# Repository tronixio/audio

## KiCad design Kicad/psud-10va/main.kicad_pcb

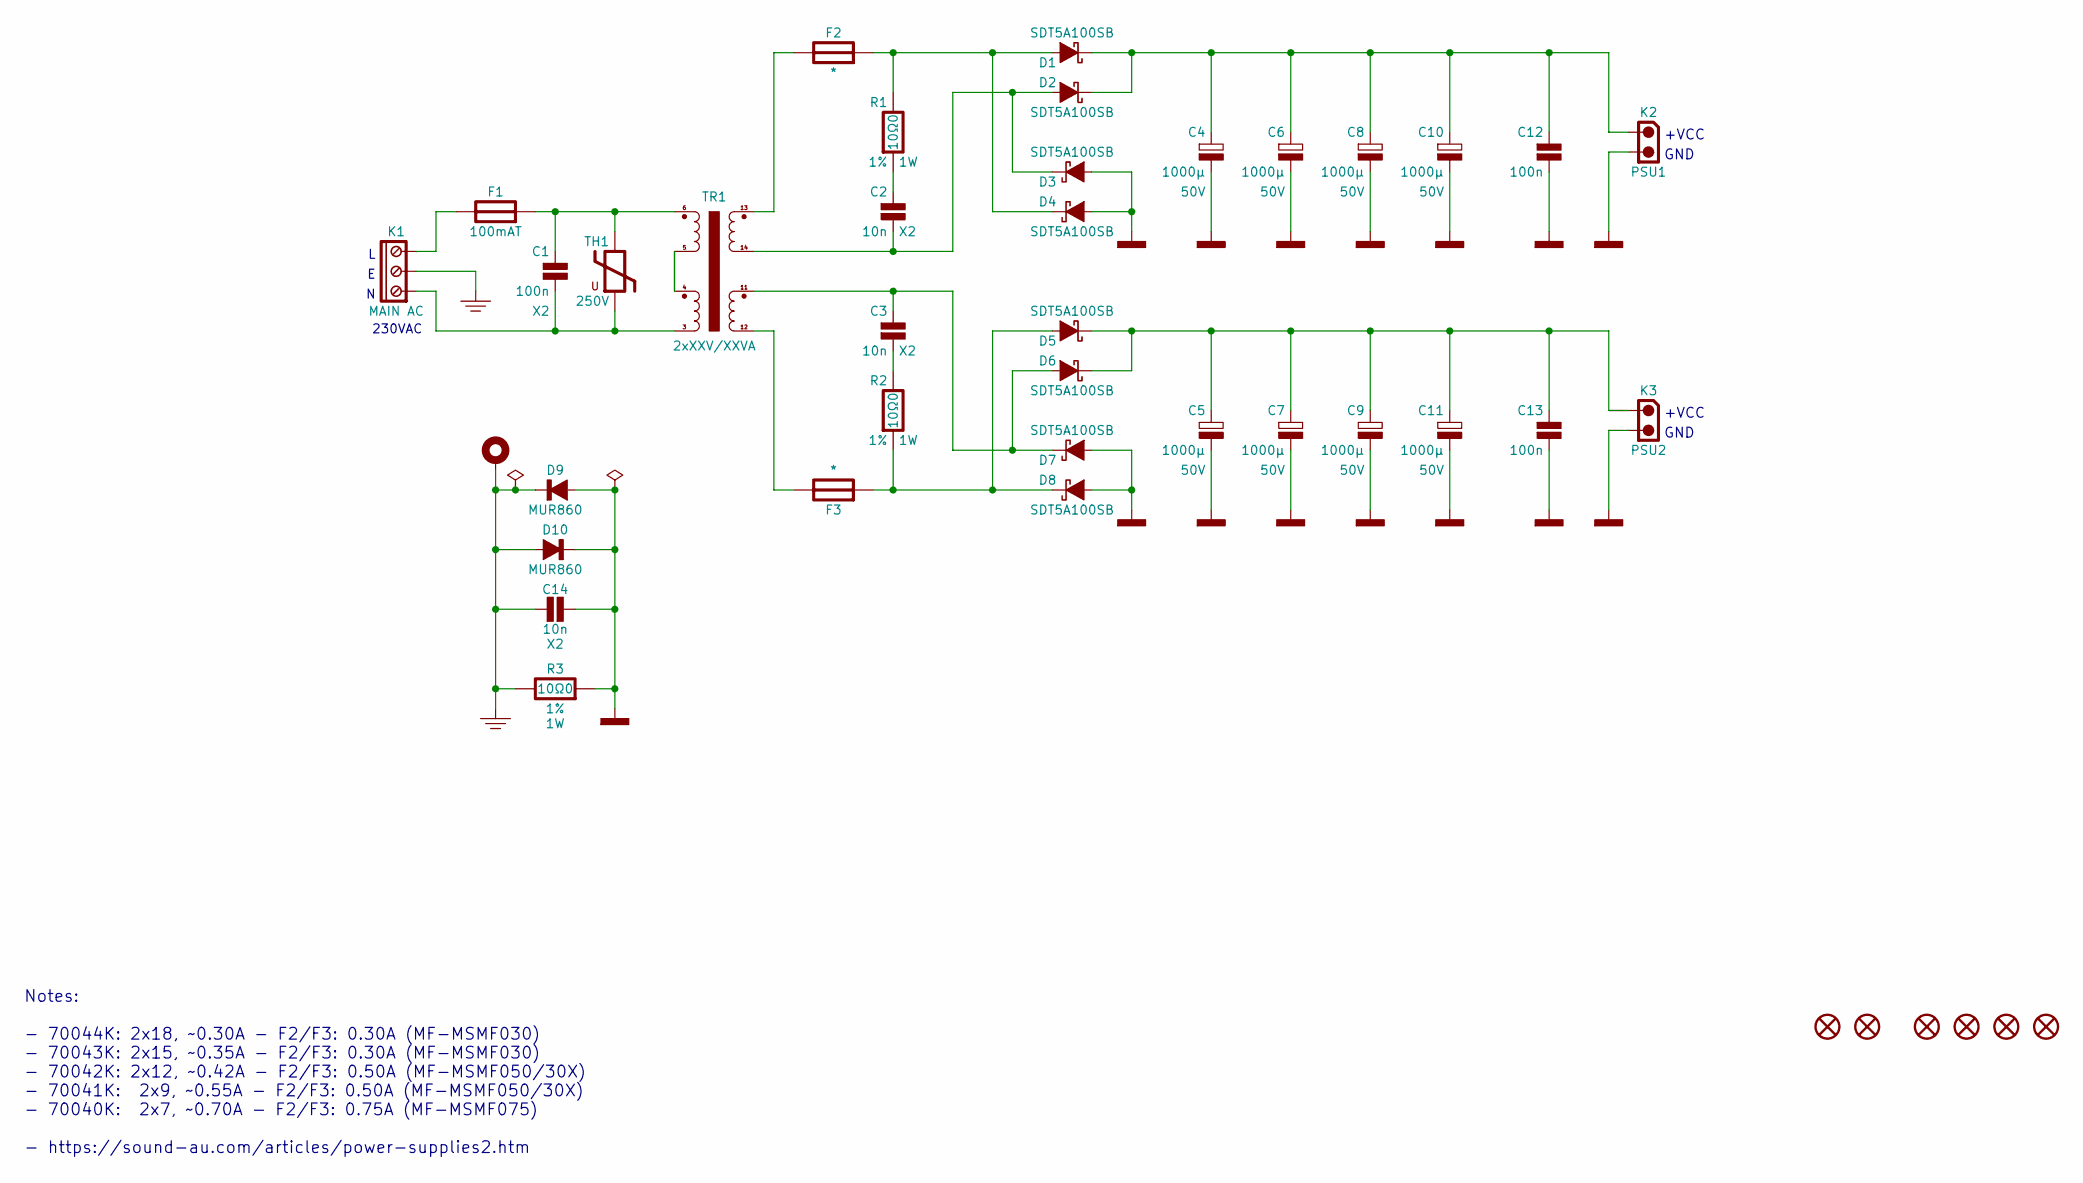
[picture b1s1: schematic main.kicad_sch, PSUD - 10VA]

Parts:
C1: 100n; WURTH-890324025017; Tolerance 10%; Voltage 275VAC; Mouser 710-890324025017
C2, C3, C14: 10n; CAPACITOR-SMD-2220; Tolerance 10%; Voltage 250VAC; Mouser 77-VJ2220Y103KXUSTX2
C4, C5, C6, C7, C8, C9, C10, C11: 1000µ; CAPACITOR-ELECTROLYTIC-RADIAL-130-250-050-WURTH; Tolerance 20%; Voltage 50V; Mouser 710-860010678024
C12, C13: 100n; CAPACITOR-SMD-1206; Tolerance 5%; Voltage 50V; Mouser 80-C1206C104J5R
D1, D2, D3, D4, D5, D6, D7, D8: SDT5A100SB; DIODE-SMB; Part Marking DXA; Mouser 621-SDT5A100SB-13
D9, D10: MUR860; DIODE-SMC; Part Marking 860JS; Mouser 771-MUR860J
F1: 100mAT; KEYSTONE-4628; Mouser 534-4628
F2, F3: *; FUSE-SMD-1812; Part Marking 75xx; Mouser 652-MF-MSMF075/24-2
F4: 100mA/SB; FUSE-CARTRIDGE-5X20; Mouser 576-0239.100MXP
F5: KEYSTONE-4628C; Mouser 534-4628C
H1: MOUNTING-HOLE-3MM-PAD-VIA
H2, H3, H4, H5: MOUNTING-HOLE-3MM-MASK
K1: MAIN AC; SAMESKY-TB005-762-03BE; Mouser 490-TB005-762-03BE
K2: PSU1; MOLEX-559320230; Mouser 538-55932-0230
K3: PSU2; MOLEX-559320230; Mouser 538-55932-0230
R1, R2, R3: 10Ω0; RESISTOR-SMD-2512; Tolerance 1%; Mouser 603-RC2512FK-0710RL
TH1: 250V; BOURNS-VARISTOR-ISOM3; Mouser 652-ISOM3-250-B-L2
TR1: 2xXXV/XXVA; TALEMA-TRANSFORMER-10VA

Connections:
EARTH: C14.1, D9.1 (C), D10.2 (A), H1.1, K1.2, R3.1
GND: C4.2, C5.2, C6.2, C7.2, C8.2, C9.2, C10.2, C11.2, C12.2, C13.2, C14.2, D3.2 (A), D4.2 (A), D7.2 (A), D8.2 (A), D9.2 (A), D10.1 (C), K2.2, K3.2, R3.2
unnamed: C1.1, F1.2, TH1.1, TR1.6
unnamed: C1.2, K1.1, TH1.2, TR1.3
unnamed: C2.1, R1.2
unnamed: C3.2, R2.1
unnamed: D1.2 (A), D4.1 (C), F2.2, R1.1
unnamed: C4.1, C6.1, C8.1, C10.1, C12.1, D1.1 (C), D2.1 (C), K2.1
unnamed: C2.2, D2.2 (A), D3.1 (C), TR1.14
unnamed: D5.2 (A), D8.1 (C), F3.2, R2.2
unnamed: C5.1, C7.1, C9.1, C11.1, C13.1, D5.1 (C), D6.1 (C), K3.1
unnamed: C3.1, D6.2 (A), D7.1 (C), TR1.11
unnamed: F1.1, K1.3
unnamed: F2.1, TR1.13
unnamed: F3.1, TR1.12
unnamed: TR1.4, TR1.5

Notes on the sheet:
+VCC
230VAC
GND
Notes: - 70044K: 2x18, ~0.30A - F2/F3: 0.30A (MF-MSMF030) - 70043K: 2x15, ~0.35A - F2/F3: 0.30A (MF-MSMF030) - 70042K: 2x12, ~0.42A - F2/F3: 0.50A (MF-MSMF050/30X) - 70041K: 2x9, ~0.55A - F2/F3: 0.50A (MF-MSMF050/30X) - 70040K: 2x7, ~0.70A - F2/F3: 0.75A (MF-MSMF075) - https://sound-au.com/articles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

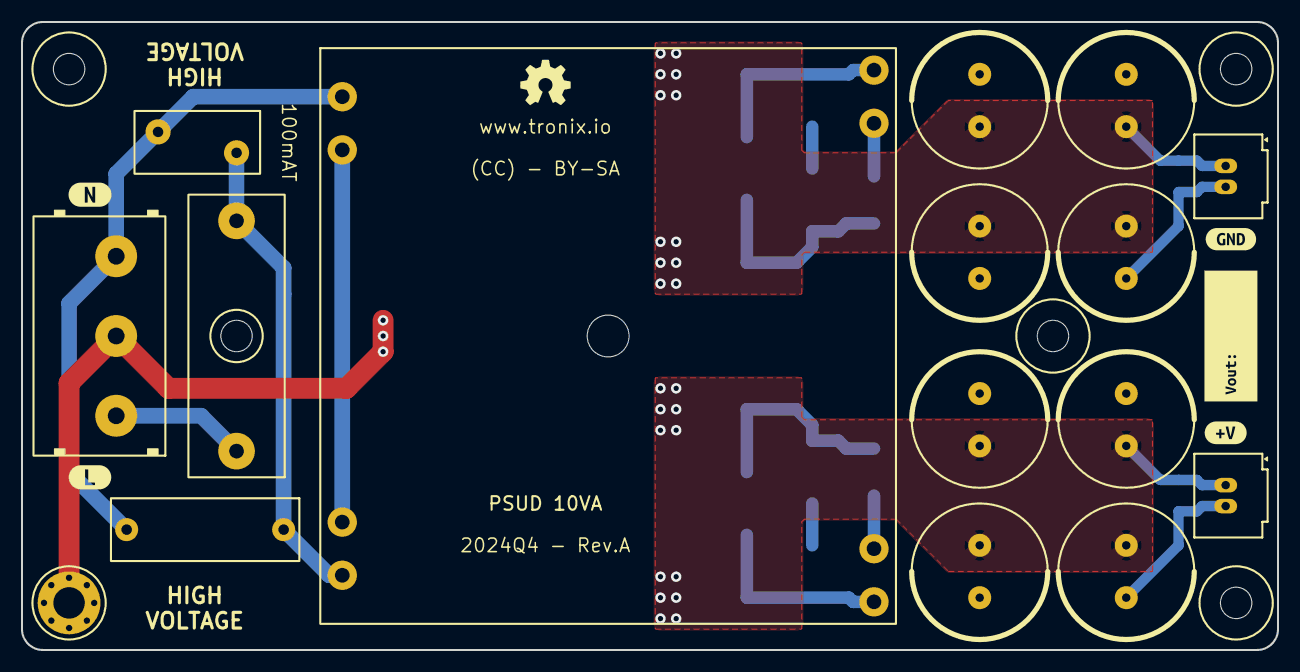
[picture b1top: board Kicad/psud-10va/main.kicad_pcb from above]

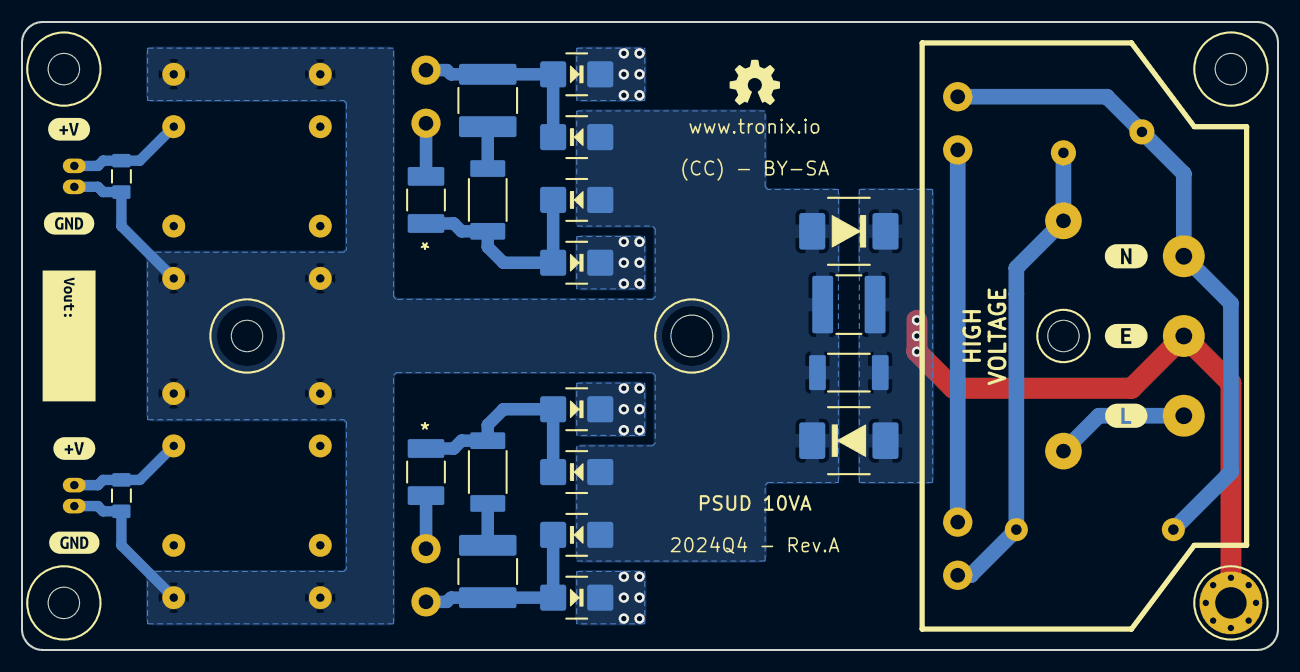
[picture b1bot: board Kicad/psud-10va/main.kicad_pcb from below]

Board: 2 copper layers, 120.0 x 60.0 mm, 57 parts (29 on the bottom side), 16 nets.

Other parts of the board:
X101, X101#2: LOGO; OSHW-5MM
kibuzzard-65E1EBC7, kibuzzard-65E1EBC7#2: G***; kibuzzard-65E1EBC7
kibuzzard-65E1EBD0, kibuzzard-65E1EBD0#2: G***; kibuzzard-65E1EBD0
kibuzzard-67C2FE8F: G***; kibuzzard-67C2FE8F
kibuzzard-67C315A4: G***; kibuzzard-67C315A4
kibuzzard-67C31590: G***; kibuzzard-67C31590
kibuzzard-67C31596: G***; kibuzzard-67C31596
kibuzzard-6735E4BF: G***; kibuzzard-6735E4BF
kibuzzard-6735E49C: G***; kibuzzard-6735E49C
kibuzzard-66229E9D, kibuzzard-66229E9D#2, kibuzzard-66229E9D#3: G***; kibuzzard-66229E9D

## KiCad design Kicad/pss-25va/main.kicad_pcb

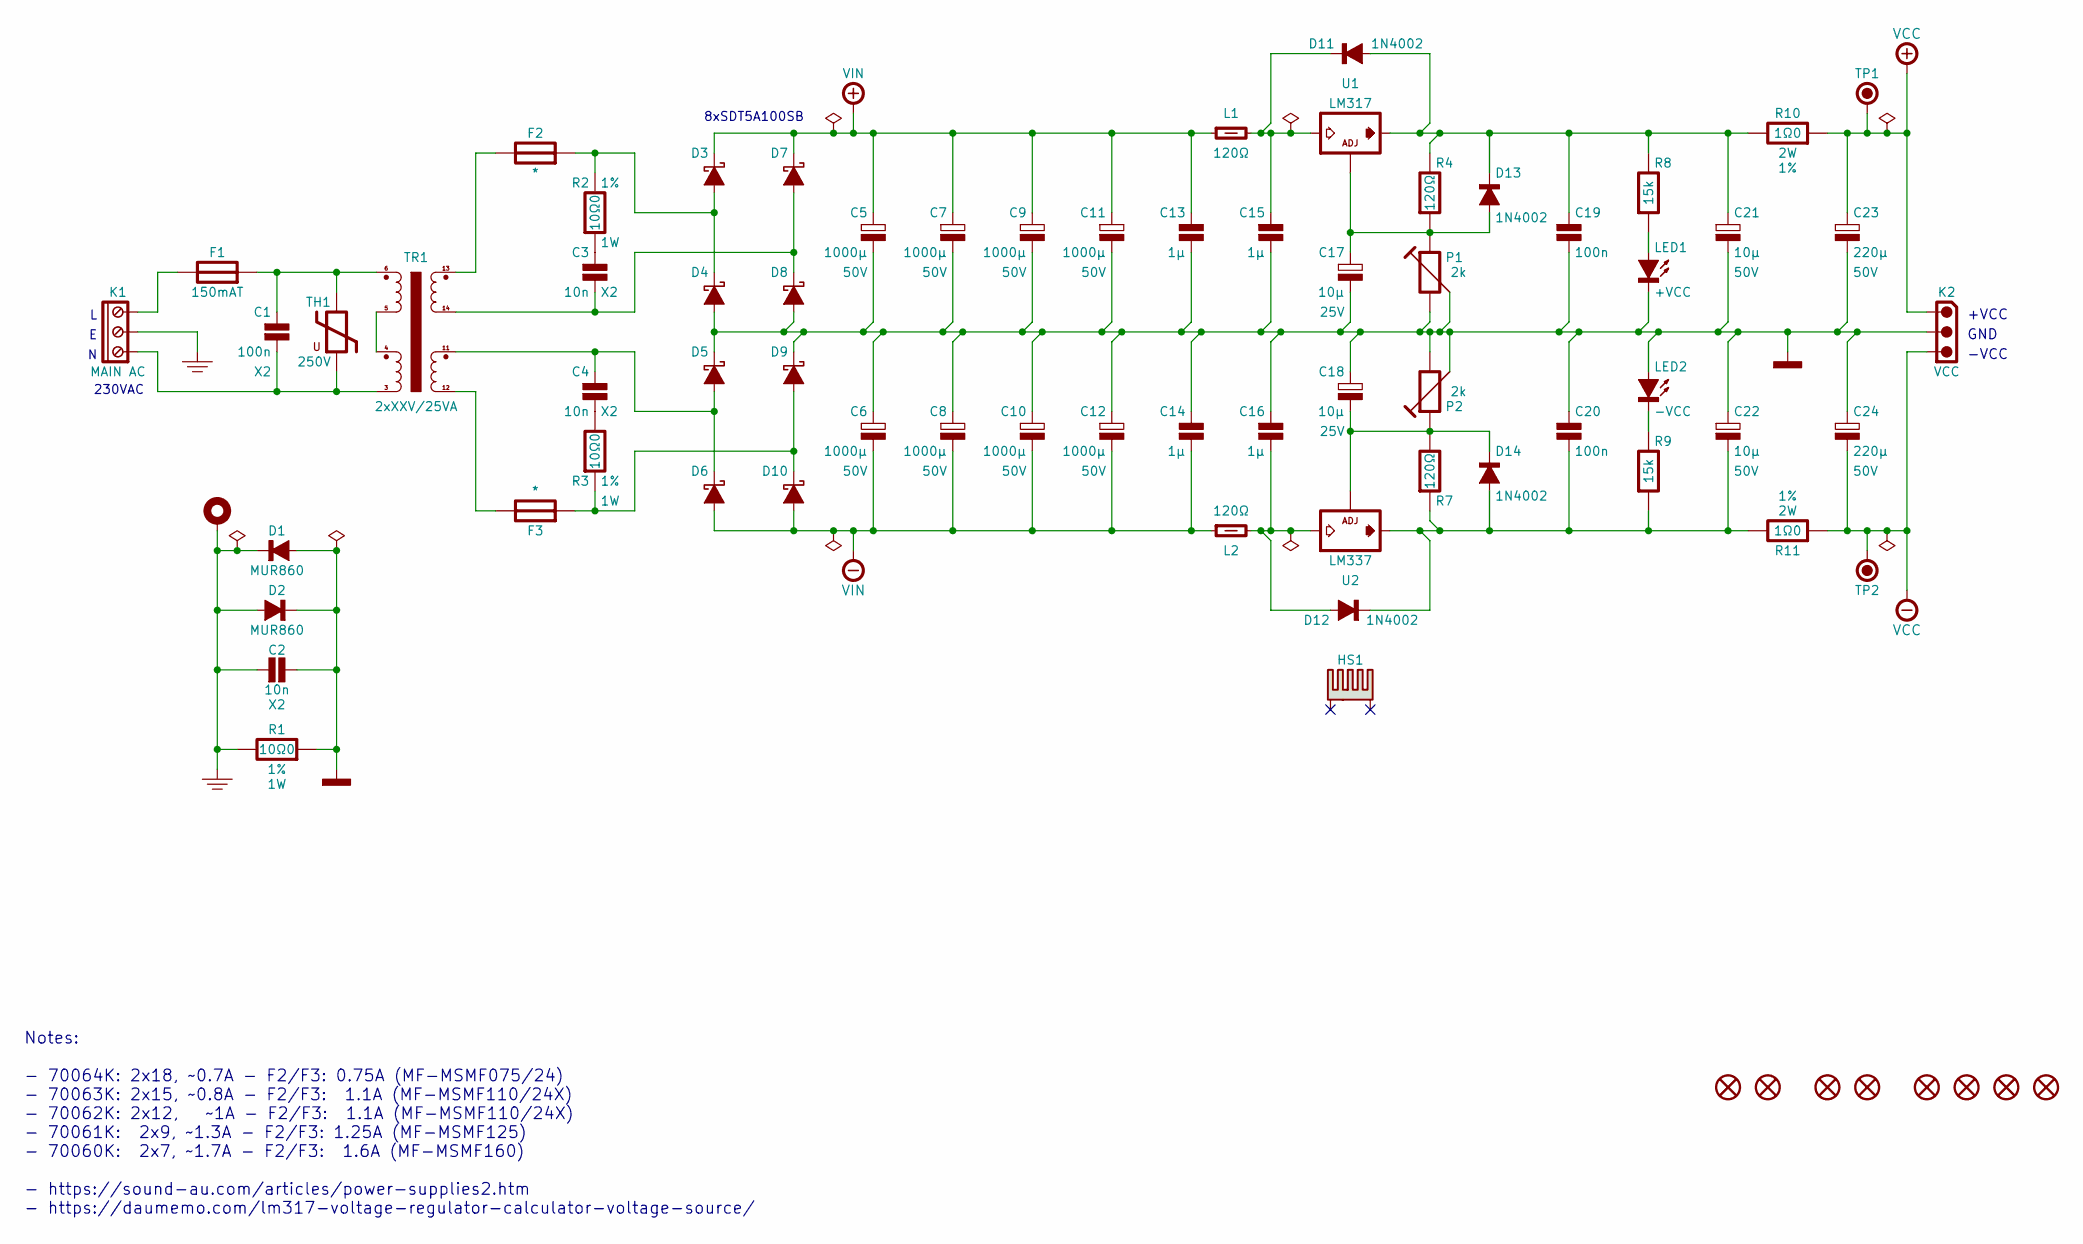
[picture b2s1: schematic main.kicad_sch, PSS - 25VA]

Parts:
C1: 100n; WURTH-890324025017; Tolerance 10%; Voltage 275VAC; Mouser 710-890324025017
C2, C3, C4: 10n; CAPACITOR-SMD-2220; Tolerance 10%; Voltage 250VAC; Mouser 77-VJ2220Y103KXUSTX2
C5, C6, C7, C8, C9, C10, C11, C12: 1000µ; CAPACITOR-ELECTROLYTIC-RADIAL-130-250-050-WURTH; Tolerance 20%; Voltage 50V; Mouser 710-860010678024
C13, C14, C15, C16: 1µ; CAPACITOR-SMD-1206; Tolerance 5%; Voltage 50V; Mouser 80-C1206C105J5
C17, C18: 10µ; CAPACITOR-SMD-CASE-B; Voltage 25V; Tolerance 10%; Mouser 74-293D106X9025B2TE3
C19, C20: 100n; CAPACITOR-SMD-1206; Tolerance 5%; Voltage 50V; Mouser 80-C1206C104J5R
C21, C22: 10µ; CAPACITOR-ELECTROLYTIC-RADIAL-050-110-020-WURTH; Tolerance 20%; Voltage 50V; Mouser 710-860240672002
C23, C24: 220µ; CAPACITOR-ELECTROLYTIC-RADIAL-100-125-050-WURTH; Tolerance 20%; Voltage 50V; Mouser 710-860010675018
D1, D2: MUR860; DIODE-SMC; Part Marking 860JS; Mouser 771-MUR860J
D3, D4, D5, D6, D7, D8, D9, D10: SDT5A100SB; DIODE-SMB; Part Marking DXA; Mouser 621-SDT5A100SB-13
D11, D12, D13, D14: 1N4002; DIODE-SMA; Part Marking A2; Mouser 583-FM4002
F1: 150mAT; KEYSTONE-4628; Mouser 534-4628
F2, F3: *; FUSE-SMD-1812; Part Marking 75xx; Mouser 652-MF-MSMF075/24-2
F4: 150mA/SB; FUSE-CARTRIDGE-5X20; Mouser 576-0239.150MXP
F5: KEYSTONE-4628C; Mouser 534-4628C
H1: MOUNTING-HOLE-3MM-PAD-VIA
H2, H3, H4, H5: MOUNTING-HOLE-3MM-MASK
HS1: OHMITE-C220-050; Mouser 588-C220-050-2AE
K1: MAIN AC; SAMESKY-TB005-762-03BE; Mouser 490-TB005-762-03BE
K2: VCC; MOLEX-559320330; Mouser 538-55932-0330
L1, L2: 120Ω; INDUCTOR-SMD-1206; Mouser 81-BLM31PG121SN1L
LED1: +VCC; LED-SMD-1206; Mouser 604-APT3216LVBCD
LED2: -VCC; LED-SMD-1206; Mouser 604-APT3216LVBCD
P1, P2: 2k; BOURNS-3314J1; Tolerance 20%; Mouser 652-3314J-1-202E
R1, R2, R3: 10Ω0; RESISTOR-SMD-2512; Tolerance 1%; Mouser 603-RC2512FK-0710RL
R4, R7: 120Ω; RESISTOR-SMD-1206; Tolerance 5%; Mouser 603-RT1206FRE07120RL
R8, R9: 15k; RESISTOR-SMD-1206; Tolerance 5%; Mouser 660-RK73B2BTTDD153J
R10, R11: 1Ω0; RESISTOR-SMD-2512; Tolerance 1%; Mouser 652-CRS2512FW1R00ELF
TH1: 250V; BOURNS-VARISTOR-ISOM3; Mouser 652-ISOM3-250-B-L2
TH2, TH3: SP400-TO200; Mouser 951-SP400-009-00-54
TP1: +VCC; TRONIXIO-TP
TP2: -VCC; TRONIXIO-TP
TR1: 2xXXV/25VA; TALEMA-TRANSFORMER-25VA
U1: LM317; TO-220-3-VERTICAL; Mouser 863-LM317TG
U2: LM337; TO-220-3-VERTICAL; Mouser 863-LM337BTG

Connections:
+VCC: C23.1, K2.1, R10.2, TP1.1
+VIN: C5.1, C7.1, C9.1, C11.1, C13.1, D3.1 (C), D7.1 (C), L1.1
-VCC: C24.2, K2.3, R11.2, TP2.1
-VIN: C6.2, C8.2, C10.2, C12.2, C14.2, D6.2 (A), D10.2 (A), L2.1
EARTH: C2.1, D1.1 (C), D2.2 (A), H1.1, K1.2, R1.1
GND: C2.2, C5.2, C6.1, C7.2, C8.1, C9.2, C10.1, C11.2, C12.1, C13.2, C14.1, C15.2, C16.1, C17.2, C18.1, C19.2, C20.1, C21.2, C22.1, C23.2, C24.1, D1.2 (A), D2.1 (C), D4.2 (A), D5.1 (C), D8.2 (A), D9.1 (C), K2.2, LED1.1 (C), LED2.2 (A), P1.1, P1.2, P2.1, P2.2, R1.2
unnamed: C1.1, F1.2, TH1.1, TR1.6
unnamed: C1.2, K1.1, TH1.2, TR1.3
unnamed: C3.1, R2.2
unnamed: C4.2, R3.1
unnamed: D3.2 (A), D4.1 (C), F2.2, R2.1
unnamed: C4.1, D5.2 (A), D6.1 (C), TR1.11
unnamed: C3.2, D7.2 (A), D8.1 (C), TR1.14
unnamed: D9.2 (A), D10.1 (C), F3.2, R3.2
unnamed: C19.1, C21.1, D11.2 (A), D13.1 (C), R4.1, R8.1, R10.1, U1.2 (VOUT)
unnamed: C15.1, D11.1 (C), L1.2, U1.3 (VIN)
unnamed: C16.2, D12.2 (A), L2.2, U2.2 (VIN)
unnamed: C20.2, C22.2, D12.1 (C), D14.2 (A), R7.2, R9.2, R11.1, U2.3 (VOUT)
unnamed: C17.1, D13.2 (A), P1.3, R4.2, U1.1 (ADJ)
unnamed: C18.2, D14.1 (C), P2.3, R7.1, U2.1 (ADJ)
unnamed: F1.1, K1.3
unnamed: F2.1, TR1.13
unnamed: F3.1, TR1.12
unnamed: LED1.2 (A), R8.2
unnamed: LED2.1 (C), R9.1
unnamed: TR1.4, TR1.5

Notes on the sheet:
8xSDT5A100SB
230VAC
GND
-VCC
+VCC
Notes: - 70064K: 2x18, ~0.7A - F2/F3: 0.75A (MF-MSMF075/24) - 70063K: 2x15, ~0.8A - F2/F3: 1.1A (MF-MSMF110/24X) - 70062K: 2x12, ~1A - F2/F3: 1.1A (MF-MSMF110/24X) - 70061K: 2x9, ~1.3A - F2/F3: 1.25A (MF-MSMF125) - 70060K: 2x7, ~1.7A - F2/F3: 1.6A (MF-MSMF160) - https://sound-au.com/articles/power-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

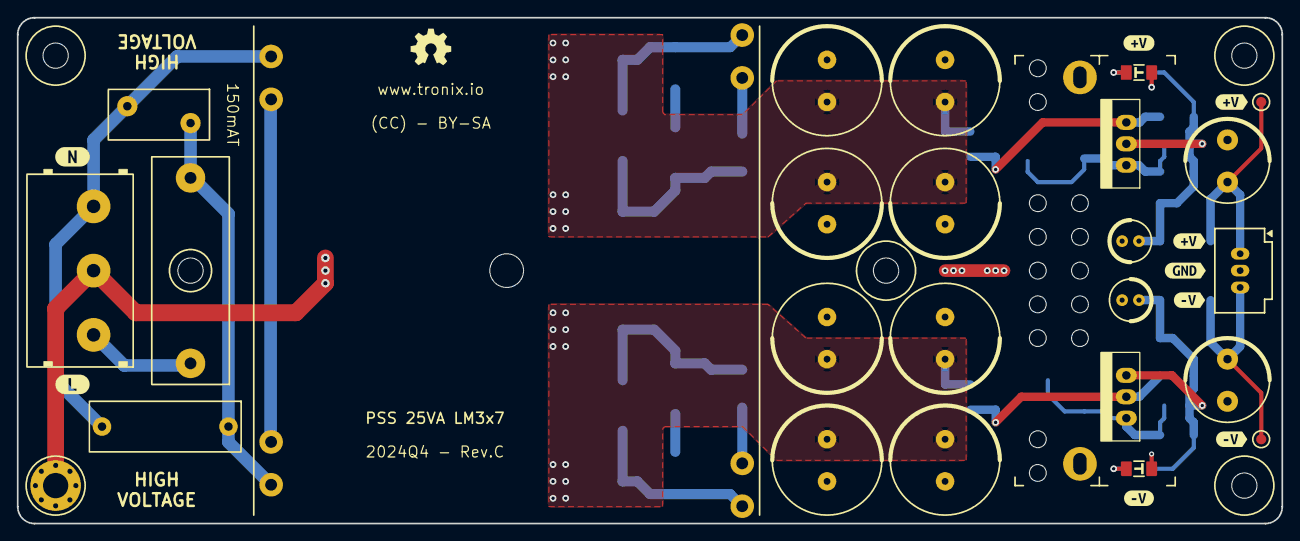
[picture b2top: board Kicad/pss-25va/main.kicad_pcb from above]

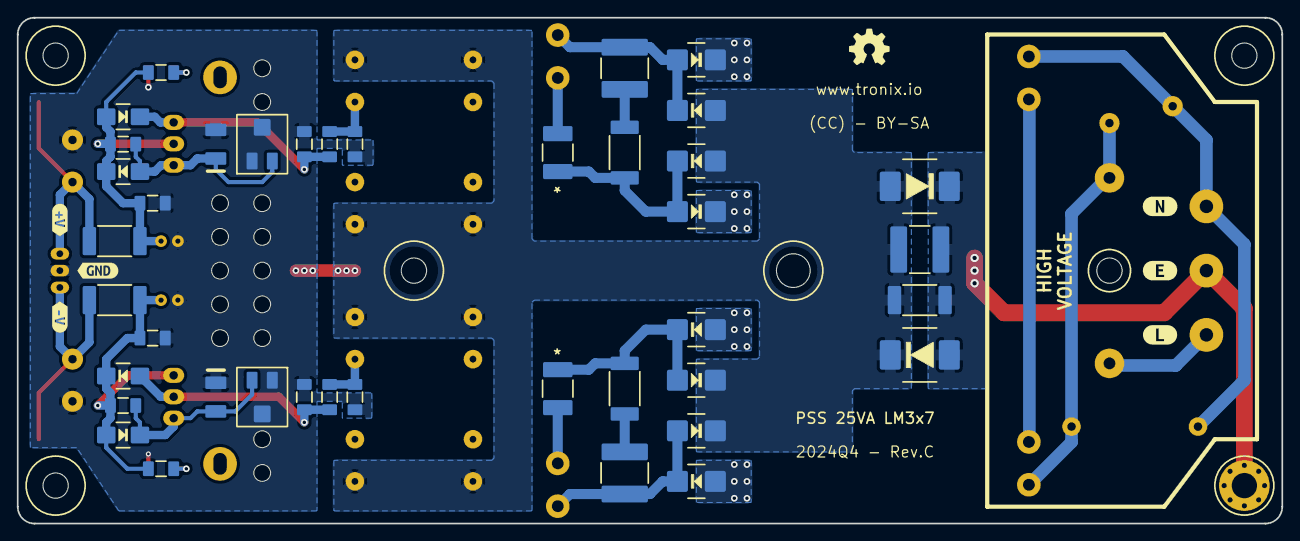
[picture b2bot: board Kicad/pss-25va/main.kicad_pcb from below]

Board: 2 copper layers, 150.0 x 60.0 mm, 89 parts (47 on the bottom side), 26 nets.

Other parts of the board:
X101, X101#2: LOGO; OSHW-5MM
kibuzzard-65E1EBC7, kibuzzard-65E1EBC7#2: G***; kibuzzard-65E1EBC7
kibuzzard-65E1EBD0, kibuzzard-65E1EBD0#2: G***; kibuzzard-65E1EBD0
kibuzzard-67C370B6: G***; kibuzzard-67C370B6
kibuzzard-67C370BE: G***; kibuzzard-67C370BE
kibuzzard-67C370C7: G***; kibuzzard-67C370C7
kibuzzard-67C370CF: G***; kibuzzard-67C370CF
kibuzzard-67C370D9: G***; kibuzzard-67C370D9
kibuzzard-67C370DF: G***; kibuzzard-67C370DF
kibuzzard-67C3709C: G***; kibuzzard-67C3709C
kibuzzard-67C36920: G***; kibuzzard-67C36920
kibuzzard-67C37093: G***; kibuzzard-67C37093
kibuzzard-6649FA9C: G***; kibuzzard-6649FA9C
kibuzzard-6649FAAE: G***; kibuzzard-6649FAAE

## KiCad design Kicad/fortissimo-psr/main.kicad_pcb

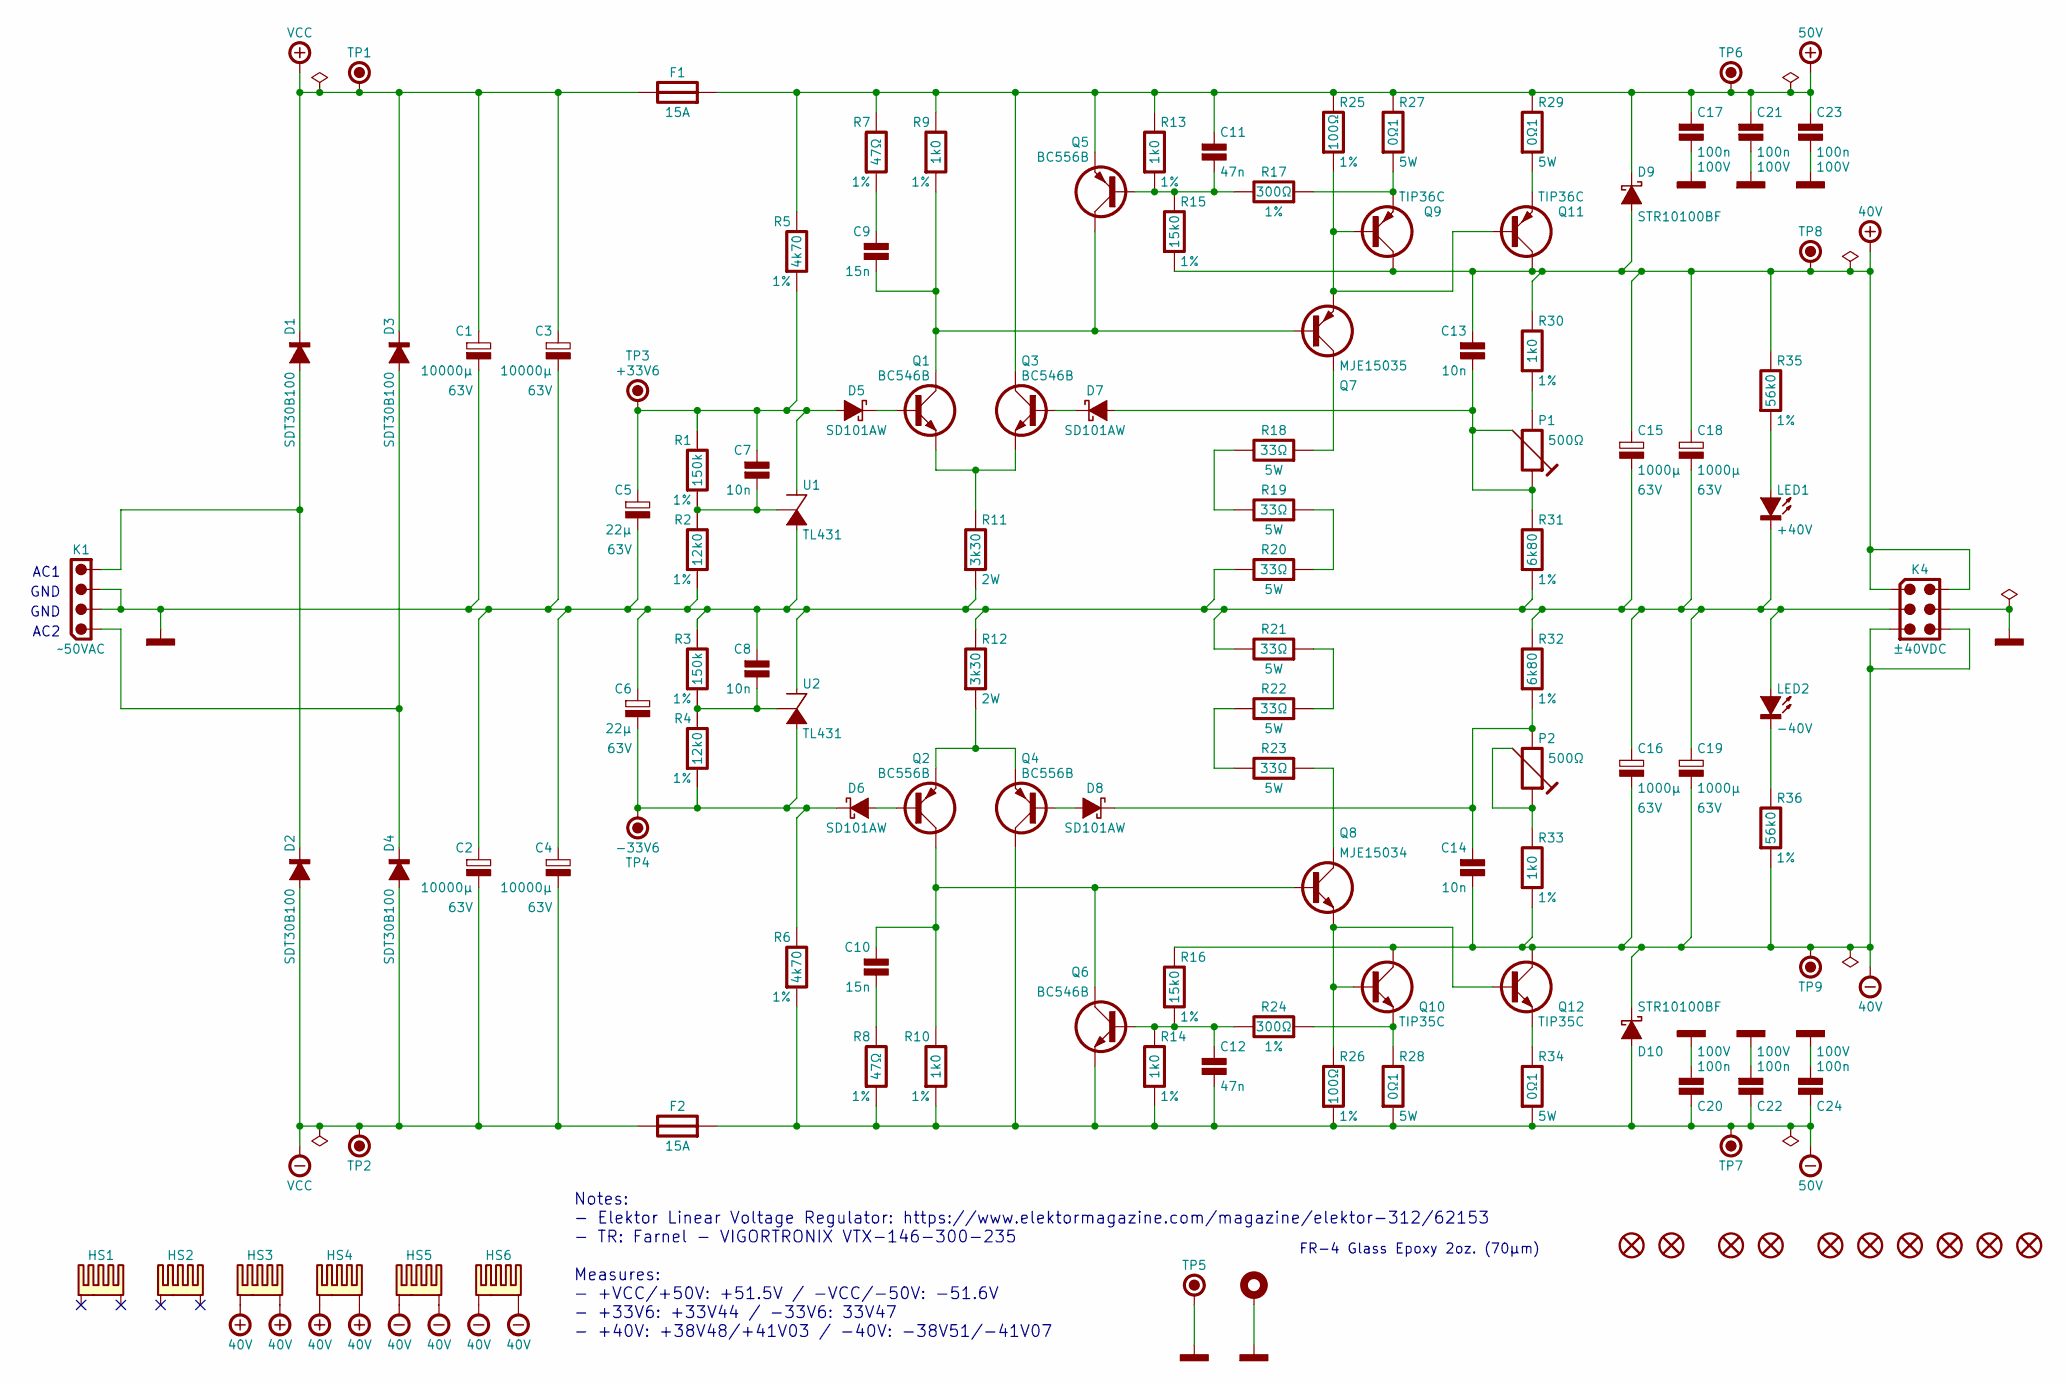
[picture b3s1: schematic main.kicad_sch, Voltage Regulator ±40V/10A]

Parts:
C1, C2, C3, C4: 10000µ; CAPACITOR-ELECTROLYTIC-RADIAL-350-520-010-WURTH; Tolerance 20%; Voltage 63V; Mouser 710-861140786024
C5, C6: 22µ; CAPACITOR-ELECTROLYTIC-RADIAL-063-110-025-WURTH; Voltage 63V; Tolerance 20%; Mouser 710-860080773004
C7, C8, C13, C14: 10n; CAPACITOR-SMD-1206; Voltage 100V; Tolerance 5%; Mouser 80-C1206C103J1R
C9, C10: 15n; CAPACITOR-SMD-1206; Voltage 100V; Tolerance 5%; Mouser 81-GRM3195C2A153JA1D
C11, C12: 47n; CAPACITOR-SMD-1206; Tolerance 5%; Voltage 100V; Mouser 603-CC126JRX7R0BB473
C15, C16, C18, C19: 1000µ; CAPACITOR-ELECTROLYTIC-RADIAL-160-250-075-WURTH; Tolerance 20%; Voltage 63V; Mouser 661-EKYB630E102ML25S
C17, C20, C21, C22, C23, C24: 100n; CAPACITOR-SMD-1206; Tolerance 5%; Voltage 100V; Mouser 80-C1206C104J1R7210
D1, D2, D3, D4: SDT30B100; TO-252-2; Mouser 621-SDT30B100D1-13
D5, D6, D7, D8: SD101AW; SOD-123; Part Marking S1/SK; Mouser 621-SD101AW-F
D9, D10: STR10100BF; DIODE-SMBF; Mouser 241-STR10100BFR10701
F1, F2: 15A; SCHURTER-OGN-3132874; Mouser 693-3-132-874
F3, F4: 15A; FUSE-CARTRIDGE-5X20; Mouser 576-0215015.MXP
H1: GND; MOUNTING-HOLE-3MM-PAD-VIA
HS1, HS2: HSE19-361616P; SAMESKY-HSE19-361616P; Mouser 179-HSE19-361616P
HS3, HS4, HS5, HS6: WAKEFIELD-657-25ABEP; Mouser 567-657-25ABEP
K1: ~50VAC; MOLEX-532580429; Mouser 538-53258-0429
K2: MIGHTY-SPOX; MOLEX-510670400; Mouser 538-51067-0400 / 538-50217-8000-CT / 53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
K3: MINI-FIT; MOLEX-39012060; Mouser 538-39-01-2060 / 538-39-00-0039 / 538-3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
K4: ±40VDC; MOLEX-39288060; Mouser 538-39-28-8060
LED1: +40V; LED-TH-ROUND-05MM; Mouser 593-VAOL-5LSBY1
LED2: -40V; LED-TH-ROUND-05MM; Mouser 593-VAOL-5LSBY1
MH1, MH2, MH3, MH4, MH5, MH6: MOUNTING-HOLE-3MM-MASK
P1, P2: 500Ω; TRIMMER-64W; Tolerance 10%; Mouser 858-67WR500LF
Q1, Q3, Q6: BC546B; TO-92-INLINE-WIDE; Mouser 512-BC546BTF
Q2, Q4, Q5: BC556B; TO-92-INLINE-WIDE; Mouser 512-BC556BTF
Q7: MJE15035; TO-220-3-VERTICAL; Mouser 863-MJE15035G
Q8: MJE15034; TO-220-3-VERTICAL; Mouser 863-MJE15034G
Q9, Q11: TIP36C; TO-247-3-VERTICAL; Mouser 511-TIP36C
Q10, Q12: TIP35C; TO-247-3-VERTICAL; Mouser 511-TIP35C
R1, R3: 150k; RESISTOR-SMD-2512; Tolerance 1%; Mouser 603-RC2512FK-07150KL
R2, R4: 12k0; RESISTOR-SMD-2512; Tolerance 1%; Mouser 603-RC2512FK-0712KL
R5, R6: 4k70; RESISTOR-SMD-2512; Tolerance 1%; Mouser 603-RC2512FK-074K7L
R7, R8: 47Ω; RESISTOR-SMD-2512; Tolerance 1%; Mouser 603-RC2512FK-0747RL
R9, R10, R13, R14, R30, R33: 1k0; RESISTOR-SMD-2512; Tolerance 1%; Mouser 603-RC2512FK-071KL
R11, R12: 3k30; RESISTOR-SMD-2512; Tolerance 5%; Mouser 279-CRGH2512J3K3
R15, R16: 15k0; RESISTOR-SMD-2512; Tolerance 1%; Mouser 603-RC2512FK-0715KL
R17, R24: 300Ω; RESISTOR-SMD-2512; Tolerance 1%; Mouser 603-RC2512FK-07300RL
R18, R19, R20, R21, R22, R23: 33Ω; TE-SQM-130-090-250-050; Tolerance 5%; Mouser 279-SQMW533RJ
R25, R26: 100Ω; RESISTOR-SMD-2512; Tolerance 1%; Mouser 603-RC2512FK-07100RL
R27, R28, R29, R34: 0Ω1; TE-SQM-130-090-250-050; Tolerance 5%; Mouser 279-SQMW5R10J
R31, R32: 6k80; RESISTOR-SMD-2512; Tolerance 1%; Mouser 603-RC2512FK-076K8L
R35, R36: 56k0; RESISTOR-SMD-2512; Tolerance 1%; Mouser 603-RC2512FK-0756KL
TP1: VCC; TRONIXIO-TP
TP2: -VCC; TRONIXIO-TP
TP3: +33V6; TRONIXIO-TP
TP4: -33V6; TRONIXIO-TP
TP5: GND; KEYSTONE-5006; Mouser 534-5006
TP6: +50V; TRONIXIO-TP
TP7: -50V; TRONIXIO-TP
TP8: +40V; TRONIXIO-TP
TP9: -40V; TRONIXIO-TP
U1, U2: TL431; TO-92-INLINE; Mouser 863-TL431BCLPG

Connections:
+40V: C13.1, C15.1, C18.1, D9.2 (A), HS3.1, HS3.2, HS4.1, HS4.2, K4.1, K4.4, Q9.2 (C), Q11.2 (C), R15.2, R30.1, R35.1, TP8.1
+50V: C11.1, C17.1, C21.1, C23.1, D9.1 (C), F1.2, Q3.1 (C), Q5.3 (E), R5.1, R7.1, R9.1, R13.1, R25.1, R27.1, R29.1, TP6.1
+VCC: C1.1, C3.1, D1.2 (C), D3.2 (C), F1.1, TP1.1
-40V: C14.2, C16.2, C19.2, D10.1 (C), HS5.1, HS5.2, HS6.1, HS6.2, K4.3, K4.6, Q10.2 (C), Q12.2 (C), R16.1, R33.2, R36.2, TP9.1
-50V: C12.2, C20.2, C22.2, C24.2, D10.2 (A), F2.2, Q4.1 (C), Q6.3 (E), R6.2, R8.2, R10.2, R14.2, R26.2, R28.2, R34.2, TP7.1
-VCC: C2.2, C4.2, D2.1 (A), D2.3 (A), D4.1 (A), D4.3 (A), F2.1, TP2.1
GND: C1.2, C2.1, C3.2, C4.1, C5.2, C6.1, C8.1, C15.2, C16.1, C17.2, C18.2, C19.1, C20.1, C21.2, C22.1, C23.2, C24.1, H1.1, K1.2, K1.3, K4.2, K4.5, LED1.1 (C), LED2.2 (A), R2.2, R3.1, R11.2, R12.1, R20.1, R21.1, R31.2, R32.1, TP5.1, U1.2 (A), U2.3 (C)
unnamed: C9.1, R7.2
unnamed: C10.2, R8.1
unnamed: D1.1 (A), D1.3 (A), D2.2 (C), K1.4
unnamed: D3.1 (A), D3.3 (A), D4.2 (C), K1.1
unnamed: C5.1, C7.1, D5.2 (A), R1.1, R5.2, TP3.1, U1.3 (C)
unnamed: D5.1 (C), Q1.2 (B)
unnamed: D6.2 (A), Q2.2 (B)
unnamed: C6.2, D6.1 (C), R4.2, R6.1, TP4.1, U2.2 (A)
unnamed: C13.2, D7.2 (A), P1.2, P1.3, R31.1
unnamed: D7.1 (C), Q3.2 (B)
unnamed: D8.2 (A), Q4.2 (B)
unnamed: C14.1, D8.1 (C), P2.1, R32.2
unnamed: LED1.2 (A), R35.2
unnamed: LED2.1 (C), R36.1
unnamed: P1.1, R30.2
unnamed: P2.2, P2.3, R33.1
unnamed: C9.2, Q1.1 (C), Q5.1 (C), Q7.1 (B), R9.2
unnamed: Q1.3 (E), Q3.3 (E), R11.1
unnamed: C10.1, Q2.1 (C), Q6.1 (C), Q8.1 (B), R10.1
unnamed: Q2.3 (E), Q4.3 (E), R12.2
unnamed: C11.2, Q5.2 (B), R13.2, R15.1, R17.1
unnamed: C12.1, Q6.2 (B), R14.1, R16.2, R24.1
unnamed: Q7.2 (C), R18.2
unnamed: Q8.2 (C), R23.2
unnamed: Q9.3 (E), R17.2, R27.2
unnamed: Q8.3 (E), Q10.1 (B), Q12.1 (B), R26.1
unnamed: Q10.3 (E), R24.2, R28.1
unnamed: Q7.3 (E), Q9.1 (B), Q11.1 (B), R25.2
unnamed: Q11.3 (E), R29.2
unnamed: Q12.3 (E), R34.1
unnamed: R18.1, R19.1
unnamed: R19.2, R20.2
unnamed: R21.2, R22.2
unnamed: R22.1, R23.1
unnamed: C7.2, R1.2, R2.1, U1.1 (R)
unnamed: C8.2, R3.2, R4.1, U2.1 (R)

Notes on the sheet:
FR-4 Glass Epoxy 2oz. (70µm)
GND
AC1
AC2
Notes: - Elektor Linear Voltage Regulator: https://www.elektormagazine.com/magazine/elektor-312/62153 - TR: Farnel - VIGORTRONIX VTX-146-300-235 Measures: - +VCC/+50V: +51.5V / -VCC/-50V: -51.6V - +33V6: +33V44 / -33V6: 33V47 - +40V: +38V48/+41V03 / -40V: -38V51/-41V07
